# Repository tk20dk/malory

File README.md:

# malory
Low power Si4432 sensor module

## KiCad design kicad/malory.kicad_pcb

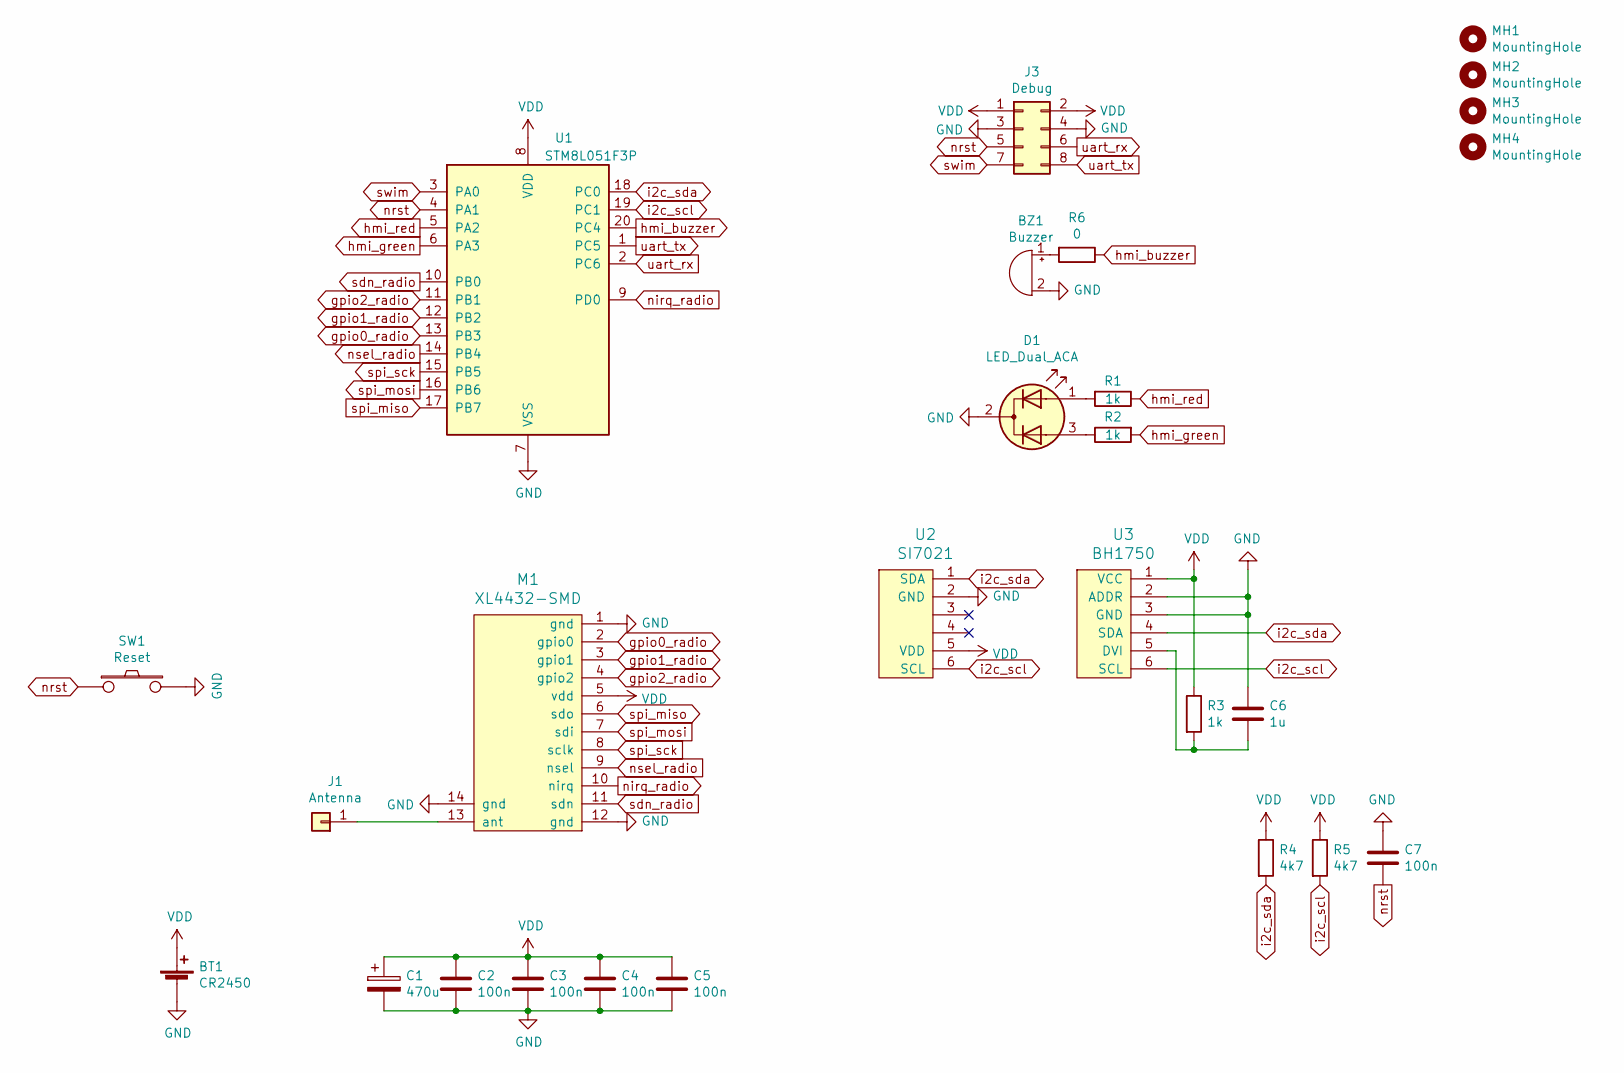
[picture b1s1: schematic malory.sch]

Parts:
BT1: CR2450; CR2450H
BZ1: Buzzer; Buzzer_12x9.5RM7.6
C1: 470u; CP_EIA-7343-15_Kemet-W
C2, C3, C4, C5, C7: 100n; C_0603_1608Metric
C6: 1u; C_0603_1608Metric
D1: LED_Dual_ACA; LED_D3.0mm-3
J1: Antenna; PinHeader_1x01_P2.54mm_Vertical
J3: Debug; PinHeader_2x04_P2.54mm_Vertical
M1: XL4432-SMD; RF4462PRO
MH1, MH2, MH3, MH4: MountingHole; MountingHole_2.5mm
R1, R2, R3: 1k; R_0603_1608Metric
R4, R5: 4k7; R_0603_1608Metric
R6: 0; R_0603_1608Metric
SW1: Reset; SW_Tactile_SKHH_Angled
U1: STM8L051F3P; TSSOP-20_4.4x6.5mm_P0.65mm
U2: SI7021
U3: BH1750

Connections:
GND: BT1.2 (-), BZ1.2 (+), C1.2, C2.2, C3.2, C4.2, C5.2, C6.1, C7.1, D1.2 (K), J3.3, J3.4, M1.1 (gnd), M1.12 (gnd), M1.14 (gnd), SW1.2, U1.7 (VSS), U2.2 (GND), U3.2 (ADDR), U3.3 (GND)
unnamed: BZ1.1 (-), R6.2
unnamed: C6.2, R3.2, U3.5 (DVI)
unnamed: D1.1 (A1), R1.2
unnamed: D1.3 (A2), R2.1
unnamed: J1.1, M1.13 (ant)
VDD: BT1.1 (+), C1.1, C2.1, C3.1, C4.1, C5.1, J3.1, J3.2, M1.5 (vdd), R3.1, R4.1, R5.1, U1.8 (VDD), U2.5 (VDD), U3.1 (VCC)
gpio0_radio: M1.2 (gpio0), U1.13 (PB3)
gpio1_radio: M1.3 (gpio1), U1.12 (PB2)
gpio2_radio: M1.4 (gpio2), U1.11 (PB1)
hmi_buzzer: R6.1, U1.20 (PC4)
hmi_green: R2.2, U1.6 (PA3)
hmi_red: R1.1, U1.5 (PA2)
i2c_scl: R5.2, U1.19 (PC1), U2.6 (SCL), U3.6 (SCL)
i2c_sda: R4.2, U1.18 (PC0), U2.1 (SDA), U3.4 (SDA)
nirq_radio: M1.10 (nirq), U1.9 (PD0)
nrst: C7.2, J3.5, SW1.1, U1.4 (PA1)
nsel_radio: M1.9 (nsel), U1.14 (PB4)
sdn_radio: M1.11 (sdn), U1.10 (PB0)
spi_miso: M1.6 (sdo), U1.17 (PB7)
spi_mosi: M1.7 (sdi), U1.16 (PB6)
spi_sck: M1.8 (sclk), U1.15 (PB5)
swim: J3.7, U1.3 (PA0)
uart_rx: J3.6, U1.2 (PC6)
uart_tx: J3.8, U1.1 (PC5)

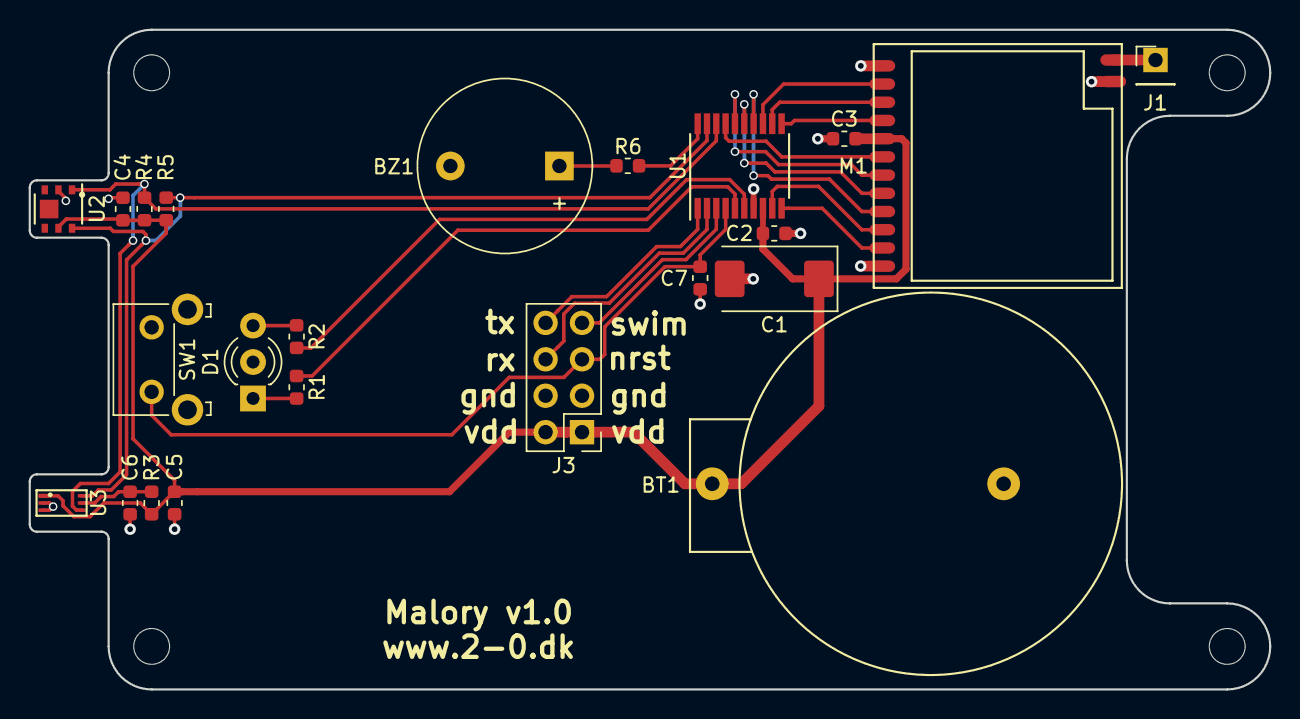
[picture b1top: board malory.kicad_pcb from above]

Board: 2 copper layers, 86.5 x 46.0 mm, 27 parts (0 on the bottom side), 25 nets.

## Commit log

2020-11-19 created initial stm8 and kicad projects
